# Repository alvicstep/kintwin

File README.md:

# KinTwin
KinTwin is a fork of [KinBP](https://github.com/DmNosachev/KinBP). It is a drop-in replacement of a controller and thumb cluster PCB boards for [Kinesis Contoured keyboards](https://deskthority.net/wiki/Kinesis_Contoured).

## Goals
- Replace stock firmware with [QMK](https://docs.qmk.fm/#/) open source firmware
- Show clear and concise BOM (bill of materials) required for the upgrade depending on Kinesis keyboard model

## Included PCBs

||
|-|
|        
| 
|  
> **Warning**  
> I have recently updated the design of thumb cluster PCB from v1.0 to v1.1 
> The changes are cosmetic and should not affect functionality, but I did not order the new boards to be able to confirm that they still work.  
> Changes include: 
> - moved silk screen of the FPC connector pad to the correct side
> - changed mounting holes of the FPC connector pad to be plated

## Comparison with KinBP
- The controller board is a simplified version on KinBP board. It uses **WeAct Studio STM32F401** development board
- KinTwin controller board uses only FPC connectors to interface with other PCB boards. In that regard it has the same design as stock Kinesis Advantage II
- KinTwin controller does not support 10-pin 2.54mm headers which are used to connect the controller to thumb cluster boards
- Similar to KinBP repo, KinTwin includes PCB boards for thumb clusters. They are functionally identical to stock Kinesis Advantage II. Unlike KinBP, these PCBs are not reversible (hence there are 2 of them). Also, similar to stock boards, they use through-hole diodes and FPC connectors
- The controller board was originally designed in KiCad by [DmNosachev](https://github.com/DmNosachev). KinTwin controller board is a clone of KinBP which was slightly modified by removing extra connector pads. 
- Thumb cluster boards were designed in [Sprint Layout 6.0](https://www.electronic-software-shop.com/lng/en/electronic-software/sprint-layout-60.html?language=en)

## Controller compatibility with top row PCBs, keywell PCBs and thumb cluster PCBs

|Keyboard Model                             |Top row PCBs|Keywell PCBs|Thumb cluster PCBs|
|-------------------------------------------|------------|------------|------------------|
|KB600 (Advantage II)                       |Yes         |Yes         |Yes               |
|KB500 (Advantage)                          |Yes         |Yes         |No  *             |
|KB13x (Essential, Classic, Professional)   |Yes         |Yes         |No  *             |
|100/110/120 **                             |No          |No          |No  *             |

\* These keyboards require custom thumb cluster PCBs which are provided in the repo\
** You are likely not going to find these keyboards in the wild. They are 20+ years old

## BOM (common for all models)
|Name                                                                |Quantity  |Image  |
|--------------------------------------------------------------------|----------|-------------------------------------------------|
|3mm Blue LED Diodes (DC 3.0V-3.2V (IF=20mA) / 0.06 Watts / 2pin)    |    4     |             |
|430ohm (For DC 6-12V) 1/4 Watt Metal Film Resistors                 |    4     |        |
|STM32F401 development board                                         |    1     ||
|Controller board                                                    |    1     |      |

## BOM (for model KB600)
|Name                                                                |Quantity  |Image  |
|--------------------------------------------------------------------|----------|-------------------------------------------------|
|13-pin straight FPC connectors                                      |    6     |       |

## BOM (for model KB500) 

|Name                                     |Quantity |Image                                               |
|-----------------------------------------|---------|----------------------------------------------------|   
|13-pin straight FPC connectors           |    8    |      |
|Left thumb cluster board                 |    1    |      |
|Right thumb cluster board                |    1    |     |
|FPC flexible flat cables (FFC1.25-60mm)  |    2    |          |
|Diodes (1N4148 DO-35 IN4148) for thumb cluster PCBs|    12   ||
|Keyboard switches for thumb cluster PCBs |    12   |        |

## BOM (for models KB13x)

|Name                                     |Quantity |Image                                                |
|-----------------------------------------|---------|-----------------------------------------------------|   
|13-pin straight FPC connectors           |    6    |       |
|13-pin angled FPC connectors             |    2    ||  
|Left thumb cluster board                 |    1    |       |
|Right thumb cluster board                |    1    |      |
|FPC flexible flat cables (FFC1.25-60mm)  |    2    |           |
|Diodes (1N4148 DO-35 IN4148) for thumb cluster PCBs|    12   | |
|Keyboard switches for thumb cluster PCBs |    12   |         |

## QMK Related Topics

Read about the custom QMK layout which I have designed [here](/layouts/readme.md)

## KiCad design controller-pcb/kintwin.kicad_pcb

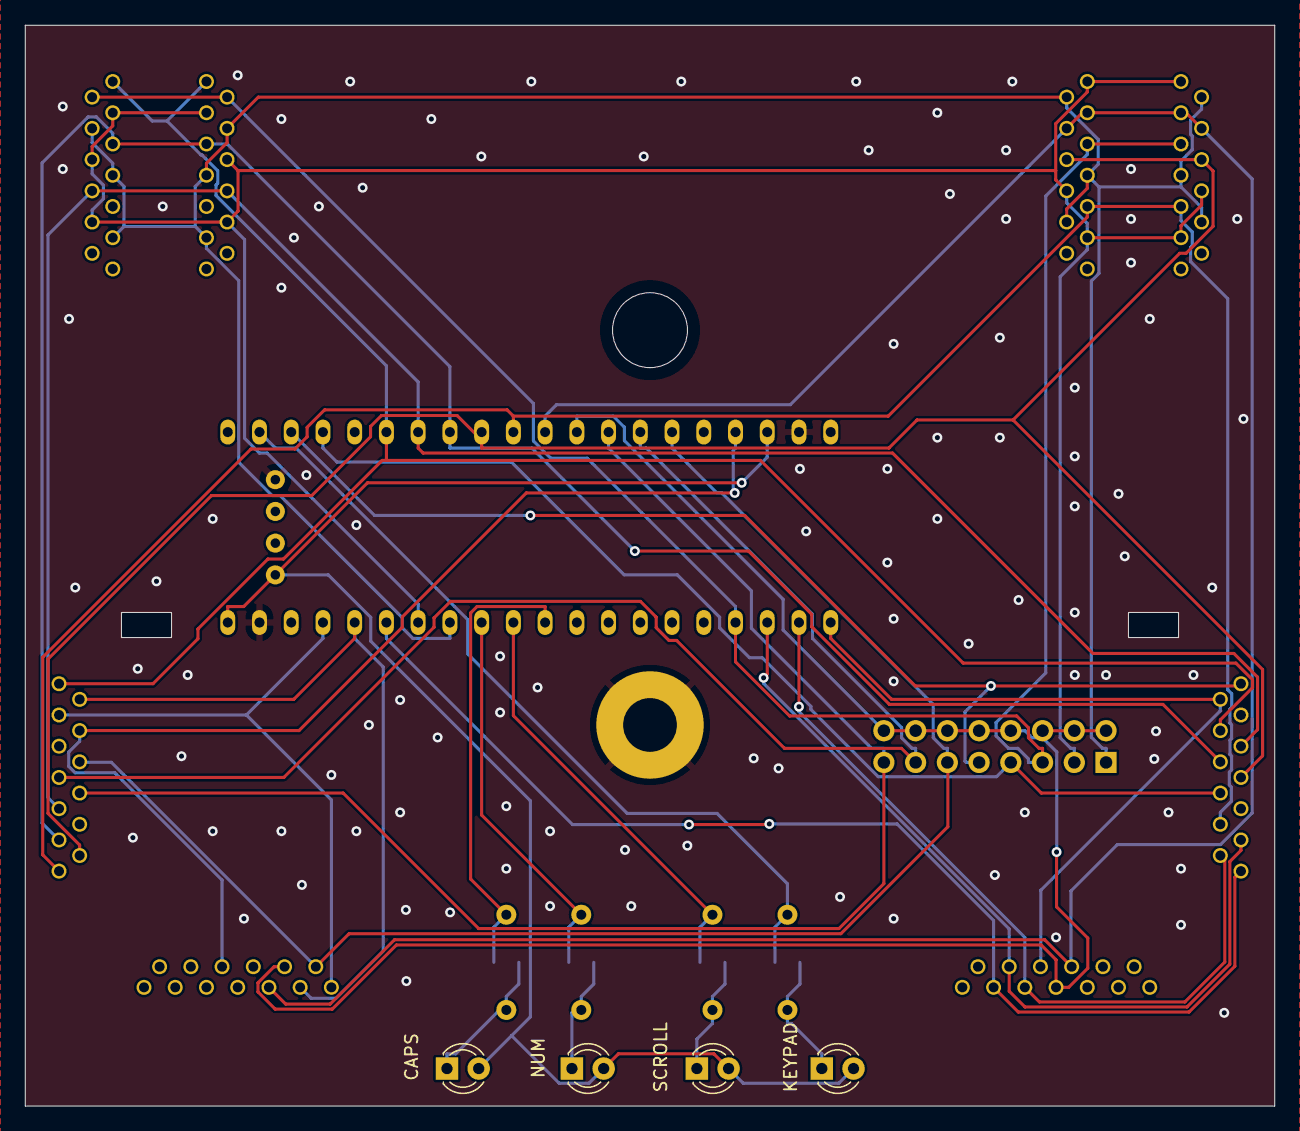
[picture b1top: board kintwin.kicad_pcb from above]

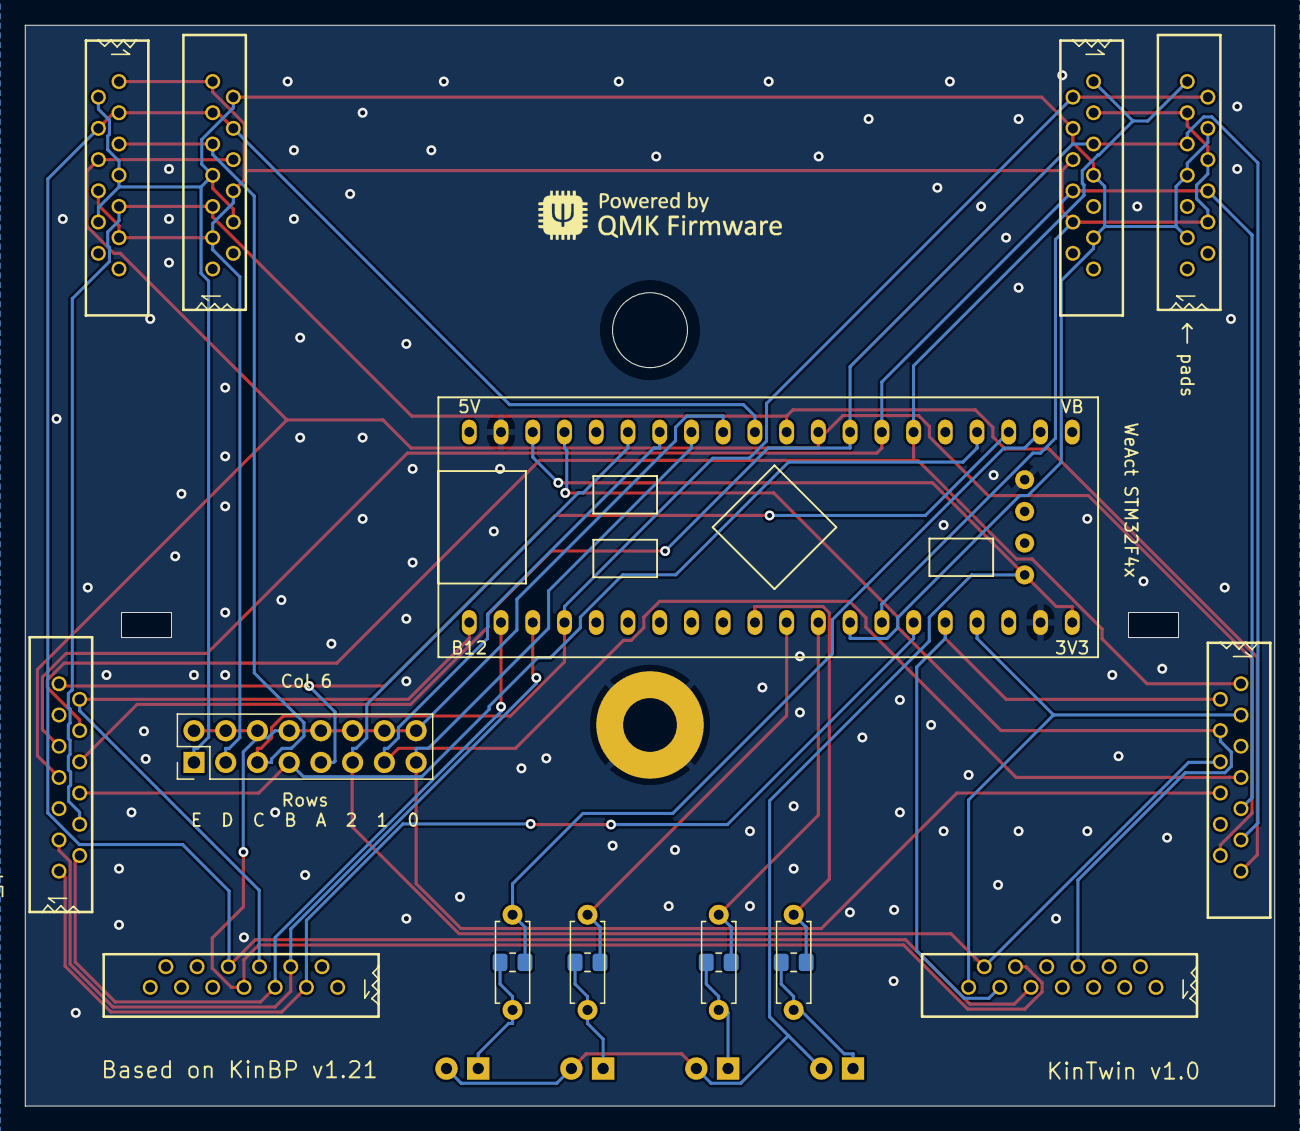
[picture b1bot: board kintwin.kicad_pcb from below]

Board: 2 copper layers, 100.0 x 86.5 mm, 24 parts (18 on the bottom side), 32 nets.

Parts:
H1: mounting pad; MountingHole_4.3mm_M4_Pad
H2: mounting pad; MountingHole_6mm
J1, J2: LEFT_TOP; 39-53-2135
J3, J4: RIGHT_TOP; 39-53-2135
J5: RIGHT_KEYWELL; 39-53-2135
J6: LEFT_KEYWELL; 39-53-2135
J9: Conn_02x08_Odd_Even; PinHeader_2x08_P2.54mm_Vertical
J10: LEFT_THUMB; 39-53-2135
J11: RIGHT_THUMB; 39-53-2135
LED1, LED2, LED3, LED4: 3mm; LED_D3.0mm
R1, R2, R3, R4: 1k; R_0805_2012Metric_Pad1.20x1.40mm_HandSolder
R5, R6, R7, R8: 1k; R_Axial_DIN0207_L6.3mm_D2.5mm_P7.62mm_Horizontal
U1: weact_STM32F4x1; STM32F4x1_MiniF4

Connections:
/3V3: LED1.2 (A), LED2.2 (A), LED3.2 (A), LED4.2 (A), U1.20 (3V3), U1.38 (3V3), U1.41 (3V3)
COL_0: J1.1, J2.13, J5.10, J6.1, U1.26 (A0)
COL_1: J1.8, J2.6, J5.9, J6.9, U1.27 (A1)
COL_2: J1.5, J2.9, J5.8, J6.11, U1.28 (A2)
COL_3: J3.6, J4.8, J5.7, J6.12, U1.29 (A3)
COL_4: J3.9, J4.5, J5.4, J6.13, U1.30 (A4)
COL_5: J3.3, J3.4, J4.10, J4.11, J10.9, J11.8, U1.31 (A5)
COL_6: J9.2, J9.4, J9.6, J9.8, J9.10, J9.12, J9.14, J9.16, J10.10, J11.7, U1.32 (A6)
GND: H1.1, U1.19 (GND), U1.39 (GND), U1.44 (GND)
LED_CAPS: R4.1, R8.1, U1.10 (A15)
LED_CAPS_R: LED4.1 (K), R4.2, R8.2
LED_KPD: R1.1, R5.1, U1.22 (C13)
LED_KPD_R: LED1.1 (K), R1.2, R5.2
LED_NUM: R3.1, R7.1, U1.12 (B4)
LED_NUM_R: LED3.1 (K), R3.2, R7.2
LED_SCRL: R2.1, R6.1, U1.11 (B3)
LED_SCRL_R: LED2.1 (K), R2.2, R6.2
ROW_0: J6.8, J9.15, U1.33 (A7)
ROW_1: J6.7, J9.13, U1.34 (B0)
ROW_2: J6.6, J9.11, J10.12, U1.35 (B1)
ROW_3: J6.4, J10.6, U1.37 (B10)
ROW_4: J6.3, J10.13, U1.17 (B9)
ROW_5: J6.2, J10.11, U1.16 (B8)
ROW_6: J5.1, J11.3, U1.15 (B7)
ROW_7: J5.3, J11.4, U1.3 (B14)
ROW_8: J5.2, J11.5, U1.2 (B13)
ROW_9: J5.12, J11.6, U1.1 (B12)
ROW_A: J5.13, J9.9, U1.23 (C14)
ROW_B: J5.6, J9.7, U1.24 (C15)
ROW_C: J1.2, J2.12, J3.5, J4.9, J9.5, U1.4 (B15)
ROW_D: J1.3, J1.6, J1.10, J2.4, J2.8, J2.11, J3.1, J3.8, J3.11, J4.3, J4.6, J4.13, J9.3, U1.14 (B6)
ROW_E: J1.4, J1.7, J1.11, J2.3, J2.7, J2.10, J3.2, J3.7, J3.10, J4.4, J4.7, J4.12, J9.1, U1.13 (B5)

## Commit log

2023-07-02 Original commit
2023-07-02 Updated wiki
2023-07-02 Generated gerber files; updated readme; added warning that the thumb board changes were not tested
2023-07-03 Added photo ot PCB
2023-07-03 Added markdown page about QMK layout
2023-07-03 Fixed keypad layer
2023-07-03 Updated screenshot of the base layer
2023-07-04 Updated layout readme
2023-07-13 Added instructions to compile/flash firmware
2023-07-13 Fixed typo
2023-07-20 test note markdown
